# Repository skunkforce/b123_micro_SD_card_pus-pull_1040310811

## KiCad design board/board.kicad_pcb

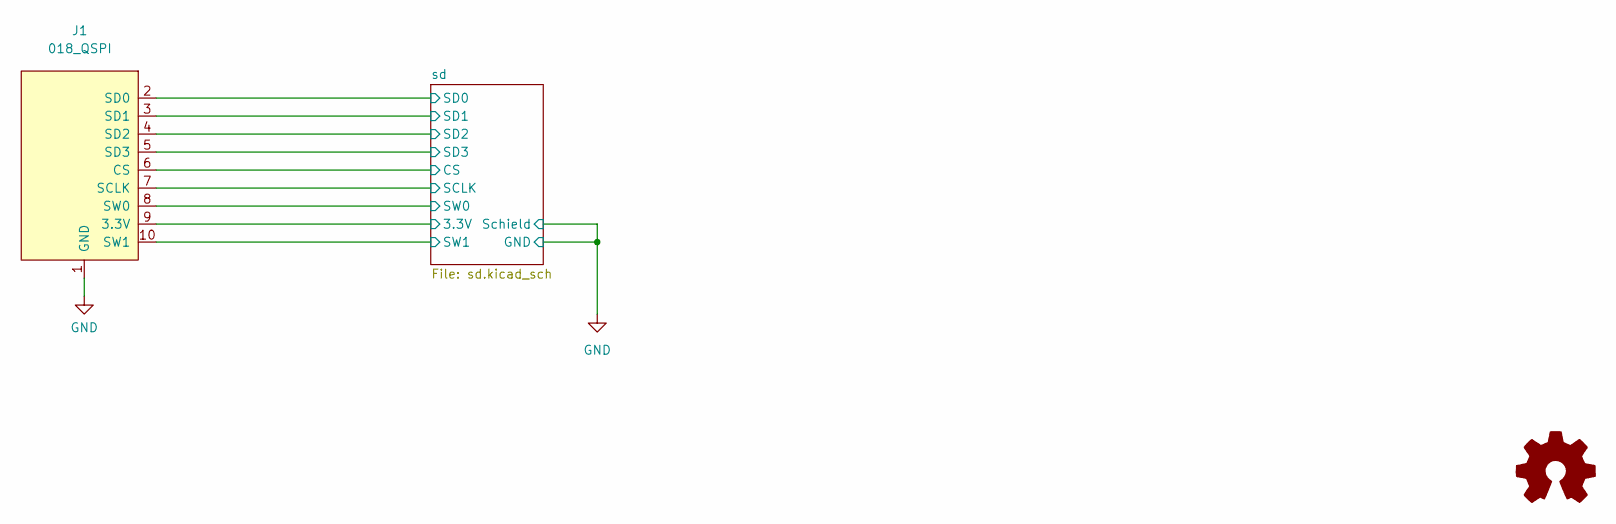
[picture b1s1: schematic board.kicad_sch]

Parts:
J1: 018_QSPI; on_edge_2x05_host
LOGO1: Logo_Open_Hardware_Small; OSHW-Symbol_6.7x6mm_SilkScreen

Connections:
/sd/3.3V: J1.9 (3.3V); also elsewhere on the board
/sd/CS: J1.6 (CS); also elsewhere on the board
/sd/SCLK: J1.7 (SCLK); also elsewhere on the board
/sd/SD0: J1.2 (SD0); also elsewhere on the board
/sd/SD1: J1.3 (SD1); also elsewhere on the board
/sd/SD2: J1.4 (SD2); also elsewhere on the board
/sd/SD3: J1.5 (SD3); also elsewhere on the board
/sd/SW0: J1.8 (SW0); also elsewhere on the board
/sd/SW1: J1.10 (SW1); also elsewhere on the board
GND: J1.1 (GND); also elsewhere on the board

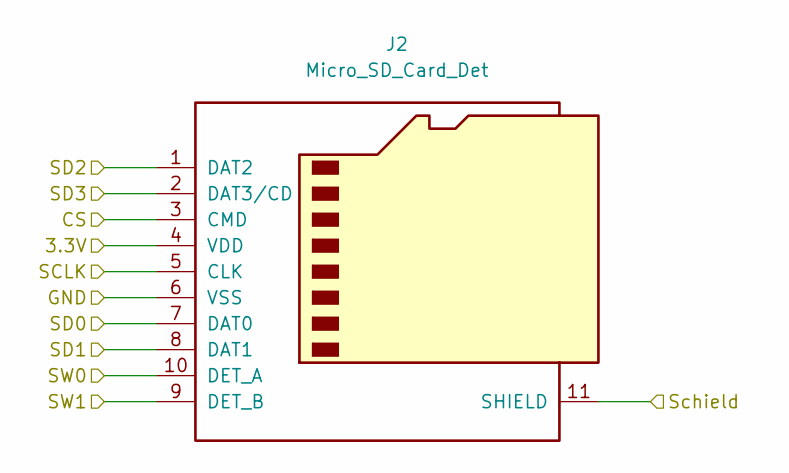
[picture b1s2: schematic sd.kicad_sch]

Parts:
J2: Micro_SD_Card_Det; microSD_HC_Molex_104031-0811; MPN 1040310811; Digi-Key_PN WM6357CT-ND

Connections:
/sd/3.3V: J2.4 (VDD); also elsewhere on the board
/sd/CS: J2.3 (CMD); also elsewhere on the board
/sd/SCLK: J2.5 (CLK); also elsewhere on the board
/sd/SD0: J2.7 (DAT0); also elsewhere on the board
/sd/SD1: J2.8 (DAT1); also elsewhere on the board
/sd/SD2: J2.1 (DAT2); also elsewhere on the board
/sd/SD3: J2.2 (DAT3/CD); also elsewhere on the board
/sd/SW0: J2.10 (DET_A); also elsewhere on the board
/sd/SW1: J2.9 (DET_B); also elsewhere on the board
GND: J2.6 (VSS), J2.11 (SHIELD); also elsewhere on the board

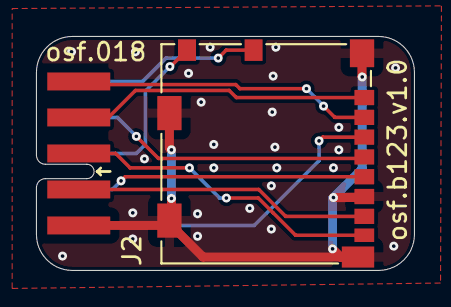
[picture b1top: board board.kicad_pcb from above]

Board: 2 copper layers, 21.0 x 13.0 mm, 3 parts (1 on the bottom side), 10 nets.

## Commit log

2023-04-03 initial
